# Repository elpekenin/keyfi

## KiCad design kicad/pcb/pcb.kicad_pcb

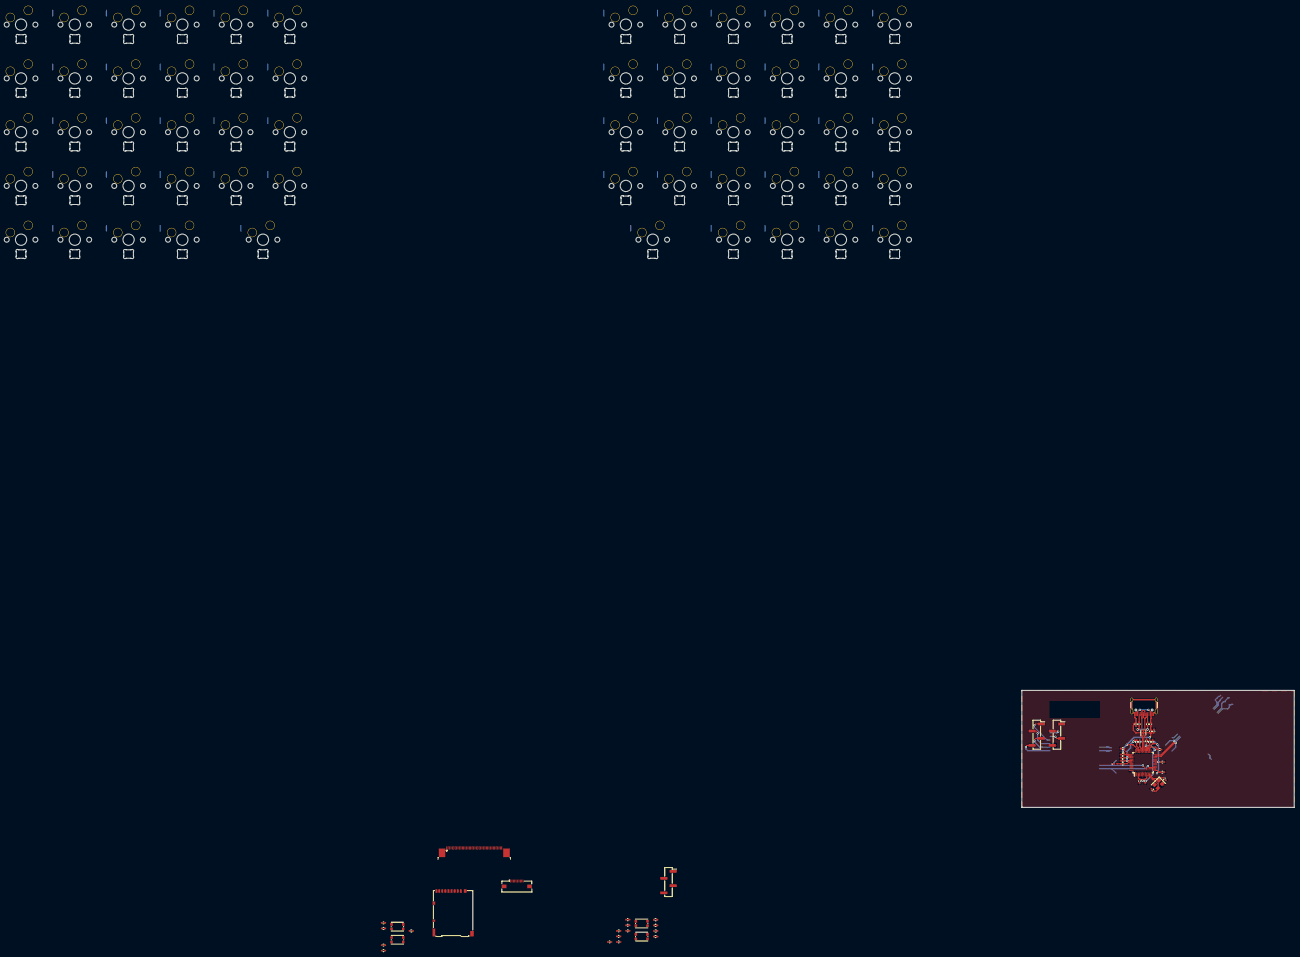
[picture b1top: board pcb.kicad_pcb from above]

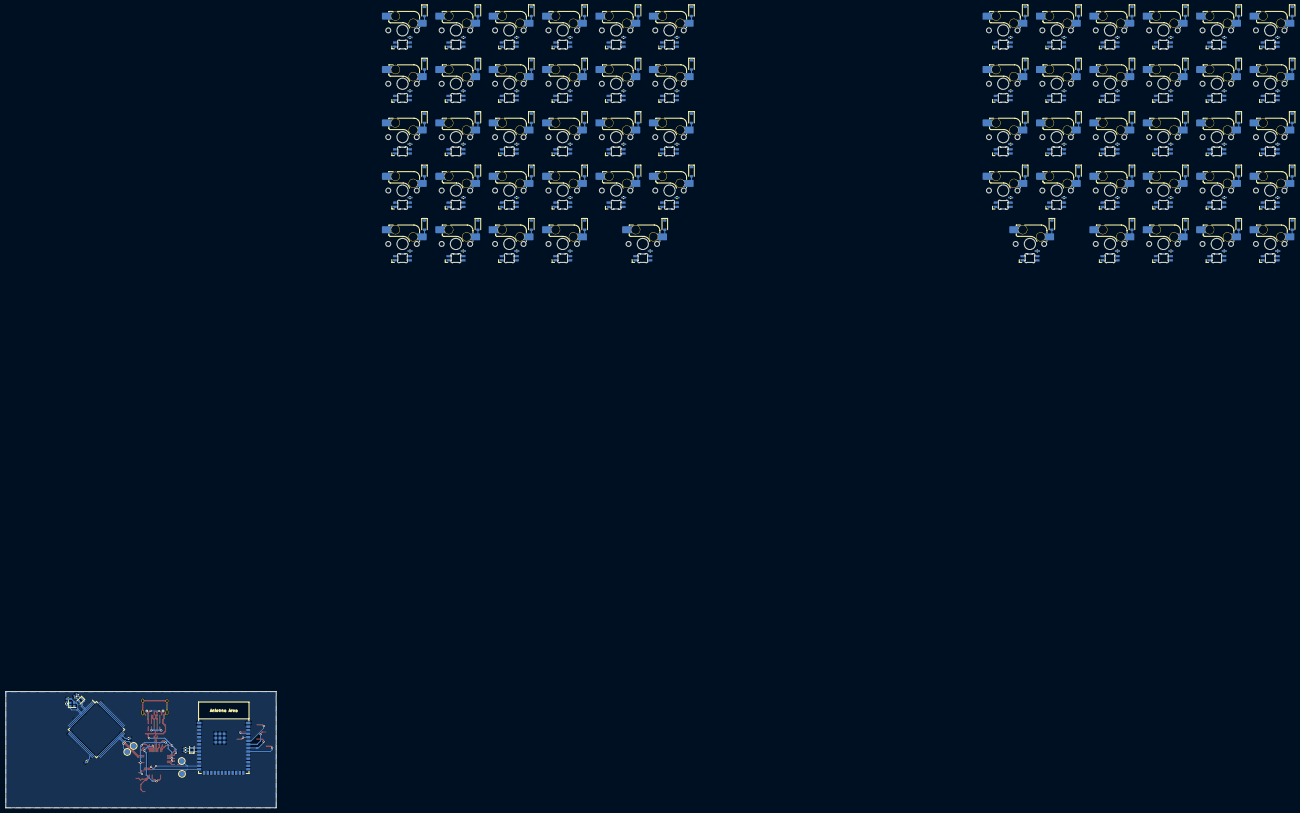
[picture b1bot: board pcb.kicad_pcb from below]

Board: 2 copper layers, 452.9 x 273.9 mm, 303 parts (249 on the bottom side), 212 nets.

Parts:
C1, C2, C3, C4, C5, C6, C7, C8, C9, C10, C11, C12, C13, C14, C15, C16, C17, C18, C19, C20, C21, C22, C23, C24, C25, C26, C27, C28, C29, C30, C31, C32, C33, C34, C35, C36, C37, C38, C39, C40, C41, C42, C43, C44, C45, C46, C47, C48, C49, C50, C51, C52, C53, C54, C55, C56, C57, C58, C64, C65, C68, C69, C70, C71, C73, C74, C75, C84, C87, C88, C89, C90, C91, C92: 100n; C_0402_1005Metric_Pad0.74x0.62mm_HandSolder
C59: 22u; C_0402_1005Metric_Pad0.74x0.62mm_HandSolder
C60, C79: 0.1u; C_0402_1005Metric_Pad0.74x0.62mm_HandSolder
C61, C63, C72: 10u; C_0402_1005Metric_Pad0.74x0.62mm_HandSolder
C66, C67, C76, C77: 12p; C_0402_1005Metric_Pad0.74x0.62mm_HandSolder
C78: C; C_0402_1005Metric_Pad0.74x0.62mm_HandSolder
C80, C81: 2.2u; C_0402_1005Metric_Pad0.74x0.62mm_HandSolder
C82, C83: 8p; C_0402_1005Metric_Pad0.74x0.62mm_HandSolder
C85, C86: 1.5p; C_0402_1005Metric_Pad0.74x0.62mm_HandSolder
D1, D2, D3, D4, D5, D6, D7, D8, D9, D10, D11, D12, D13, D14, D15, D16, D17, D18, D19, D20, D21, D22, D23, D24, D25, D26, D27, D28, D29, D30, D31, D32, D33, D34, D35, D36, D37, D38, D39, D40, D41, D42, D43, D44, D45, D46, D47, D48, D49, D50, D51, D52, D53, D54, D55, D56, D57, D58: 1N4148W; D_SOD-123
D59: HUB LED; LED_0402_1005Metric_Pad0.77x0.64mm_HandSolder
F1: 750 mA; Fuse_0402_1005Metric_Pad0.77x0.64mm_HandSolder
J1: ESP JTAG; PinHeader_1x04_P2.54mm_Vertical_SMD_Pin1Right
J2: USB Connector; USB_C_Receptacle_HRO_TYPE-C-31-M-12
J3: ESP UART; PinHeader_1x04_P2.54mm_Vertical_SMD_Pin1Right
J4: SD Card; microSD_HC_Hirose_DM3AT-SF-PEJM5
J5: LTDC Screen; TE_4-1734839-0_1x40-1MP_P0.5mm_Horizontal
J6: LS0XX; Molex_54548-1071_1x10-1MP_P0.5mm_Horizontal
J7: STM Debug; PinHeader_1x04_P2.54mm_Vertical_SMD_Pin1Right
L1, L2: L_Ferrite; L_0402_1005Metric_Pad0.77x0.64mm_HandSolder
LED1, LED2, LED3, LED4, LED5, LED6, LED7, LED8, LED9, LED10, LED11, LED12, LED13, LED14, LED15, LED16, LED17, LED18, LED19, LED20, LED21, LED22, LED23, LED24, LED25, LED26, LED27, LED28, LED29, LED30, LED31, LED32, LED33, LED34, LED35, LED36, LED37, LED38, LED39, LED40, LED41, LED42, LED43, LED44, LED45, LED46, LED47, LED48, LED49, LED50, LED51, LED52, LED53, LED54, LED55, LED56, LED57, LED58: MX_SK6812MINI-E; LED_MX_6028R
MX1, MX2, MX3, MX4, MX5, MX6, MX7, MX8, MX9, MX10, MX11, MX12, MX13, MX14, MX15, MX16, MX17, MX18, MX19, MX20, MX21, MX22, MX23, MX24, MX25, MX26, MX27, MX28, MX29, MX30, MX31, MX32, MX33, MX34, MX35, MX36, MX37, MX38, MX39, MX40, MX41, MX42, MX43, MX44, MX45, MX46, MX47, MX48, MX49, MX50, MX51, MX52, MX53, MX54, MX55, MX56, MX57, MX58: MX_SW_HS; SW_MX_HS_1u
R1, R9: R; R_0402_1005Metric_Pad0.72x0.64mm_HandSolder
R6: 2K7; R_0402_1005Metric_Pad0.72x0.64mm_HandSolder
R7, R13, R15, R18: 10K; R_0402_1005Metric_Pad0.72x0.64mm_HandSolder
R11, R12: 5K1; R_0402_1005Metric_Pad0.72x0.64mm_HandSolder
R16, R17: 22R; R_0402_1005Metric_Pad0.72x0.64mm_HandSolder
SW1: ESP Boot; SW_Push_1P1T_NO_CK_KMR2
SW2: ESP Rst; SW_Push_1P1T_NO_CK_KMR2
SW3: STM Boot; SW_Push_1P1T_NO_CK_KMR2
SW4: STM Rst; SW_Push_1P1T_NO_CK_KMR2
TP1, TP2, TP3, TP4: TestPoint; TestPoint_Pad_D2.0mm
U1: FE1.1; LQFP-48_7x7mm_P0.5mm
U2: STM32H750VBTx; LQFP-100_14x14mm_P0.5mm
U3: ESP32-S3-WROOM-2
U6: USBLC6-2P6; SOT-666
Y1: 12 MHz; Crystal_SMD_3225-4Pin_3.2x2.5mm
Y2, Y4: 32.768 KHz; Crystal_SMD_2012-2Pin_2.0x1.2mm
Y3: 25 MHz; Crystal_SMD_2016-4Pin_2.0x1.6mm

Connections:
+3V3: C59.1, C60.1, C84.1, C87.1, C88.1, C89.1, C90.1, C91.1, C92.1, J3.1, J4.4 (VDD), J5.4, J7.1, R9.1, R18.2, SW3.1, U2.6 (VBAT), U2.11 (VDD), U2.21 (VDDA), U2.27 (VDD), U2.50 (VDD), U2.75 (VDD), U2.100 (VDD), U3.2 (3V3)
+5V: C1.1, C2.1, C3.1, C4.1, C5.1, C6.1, C7.1, C8.1, C9.1, C10.1, C11.1, C12.1, C13.2, C14.2, C15.2, C16.2, C17.2, C18.2, C19.2, C20.2, C21.2, C22.2, C23.2, C24.2, C25.1, C26.1, C27.1, C28.1, C29.1, C30.1, C31.1, C32.1, C33.1, C34.1, C35.1, C36.1, C37.2, C38.2, C39.2, C40.2, C41.2, C42.2, C43.2, C44.2, C45.2, C46.2, C47.2, C48.2, C49.1, C50.1, C51.1, C52.1, C53.1, C54.1, C55.1, C56.1, C57.1, C58.1, C61.2, C65.2, F1.2, J5.1, J5.2, LED1.1 (VDD), LED2.1 (VDD), LED3.1 (VDD), LED4.1 (VDD), LED5.1 (VDD), LED6.1 (VDD), LED7.1 (VDD), LED8.1 (VDD), LED9.1 (VDD), LED10.1 (VDD), LED11.1 (VDD), LED12.1 (VDD), LED13.1 (VDD), LED14.1 (VDD), LED15.1 (VDD), LED16.1 (VDD), LED17.1 (VDD), LED18.1 (VDD), LED19.1 (VDD), LED20.1 (VDD), LED21.1 (VDD), LED22.1 (VDD), LED23.1 (VDD), LED24.1 (VDD), LED25.1 (VDD), LED26.1 (VDD), LED27.1 (VDD), LED28.1 (VDD), LED29.1 (VDD), LED30.1 (VDD), LED31.1 (VDD), LED32.1 (VDD), LED33.1 (VDD), LED34.1 (VDD), LED35.1 (VDD), LED36.1 (VDD), LED37.1 (VDD), LED38.1 (VDD), LED39.1 (VDD), LED40.1 (VDD), LED41.1 (VDD), LED42.1 (VDD), LED43.1 (VDD), LED44.1 (VDD), LED45.1 (VDD), LED46.1 (VDD), LED47.1 (VDD), LED48.1 (VDD), LED49.1 (VDD), LED50.1 (VDD), LED51.1 (VDD), LED52.1 (VDD), LED53.1 (VDD), LED54.1 (VDD), LED55.1 (VDD), LED56.1 (VDD), LED57.1 (VDD), LED58.1 (VDD), U1.35 (VBUSM), U1.38 (VD5_IN), U6.5 (VBUS)
COL_0: MX1.2, MX13.2, MX25.2, MX37.2, MX49.2
COL_1: MX2.2, MX14.2, MX26.2, MX38.2, MX50.2
COL_2: MX3.2, MX15.2, MX27.2, MX39.2, MX51.2
COL_3: MX4.2, MX16.2, MX28.2, MX40.2, MX52.2
COL_4: MX5.2, MX17.2, MX29.2, MX41.2, MX53.2
COL_5: MX6.2, MX18.2, MX30.2, MX42.2
COL_6: MX7.2, MX19.2, MX31.2, MX43.2, MX54.2
COL_7: MX8.2, MX20.2, MX32.2, MX44.2
COL_8: MX9.2, MX21.2, MX33.2, MX45.2, MX55.2
COL_9: MX10.2, MX22.2, MX34.2, MX46.2, MX56.2
COL_10: MX11.2, MX23.2, MX35.2, MX47.2, MX57.2
COL_11: MX12.2, MX24.2, MX36.2, MX48.2, MX58.2
ESP D+: TP3.1, U1.15 (DP4), U3.14 (GPIO20/U1CTS/ADC2_CH9/CLK_OUT1/USB_D+)
ESP D-: TP4.1, U1.14 (DM4), U3.13 (GPIO19/U1RTS/ADC2_CH8/CLK_OUT2/USB_D-)
ESP EN: C78.2, C79.2, R9.2, SW2.2, U3.3 (EN)
Earth: J2.A1 (GND), J2.A12 (GND), J2.B1 (GND), J2.B12 (GND), J2.S1 (SHIELD), L1.1, U6.2 (GND)
GND: C1.2, C2.2, C3.2, C4.2, C5.2, C6.2, C7.2, C8.2, C9.2, C10.2, C11.2, C12.2, C13.1, C14.1, C15.1, C16.1, C17.1, C18.1, C19.1, C20.1, C21.1, C22.1, C23.1, C24.1, C25.2, C26.2, C27.2, C28.2, C29.2, C30.2, C31.2, C32.2, C33.2, C34.2, C35.2, C36.2, C37.1, C38.1, C39.1, C40.1, C41.1, C42.1, C43.1, C44.1, C45.1, C46.1, C47.1, C48.1, C49.2, C50.2, C51.2, C52.2, C53.2, C54.2, C55.2, C56.2, C57.2, C58.2, C59.2, C60.2, C61.1, C63.2, C64.2, C65.1, C66.1, C67.2, C68.2, C69.2, C70.2, C71.2, C72.2, C73.2, C74.2, C75.2, C76.1, C77.2, C78.1, C79.1, C80.2, C81.1, C82.1, C83.2, C84.2, C85.1, C86.2, C87.2, C88.2, C89.2, C90.2, C91.2, C92.2, D59.1 (K), J3.4, J4.6 (VSS), J4.10 (SHIELD), J5.3, J5.29, J5.36, J7.4, L1.2, LED1.4 (VSS), LED2.4 (VSS), LED3.4 (VSS), LED4.4 (VSS), LED5.4 (VSS), LED6.4 (VSS), LED7.4 (VSS), LED8.4 (VSS), LED9.4 (VSS), LED10.4 (VSS), LED11.4 (VSS), LED12.4 (VSS), LED13.4 (VSS), LED14.4 (VSS), LED15.4 (VSS), LED16.4 (VSS), LED17.4 (VSS), LED18.4 (VSS), LED19.4 (VSS), LED20.4 (VSS), LED21.4 (VSS), LED22.4 (VSS), LED23.4 (VSS), LED24.4 (VSS), LED25.4 (VSS), LED26.4 (VSS), LED27.4 (VSS), LED28.4 (VSS), LED29.4 (VSS), LED30.4 (VSS), LED31.4 (VSS), LED32.4 (VSS), LED33.4 (VSS), LED34.4 (VSS), LED35.4 (VSS), LED36.4 (VSS), LED37.4 (VSS), LED38.4 (VSS), LED39.4 (VSS), LED40.4 (VSS), LED41.4 (VSS), LED42.4 (VSS), LED43.4 (VSS), LED44.4 (VSS), LED45.4 (VSS), LED46.4 (VSS), LED47.4 (VSS), LED48.4 (VSS), LED49.4 (VSS), LED50.4 (VSS), LED51.4 (VSS), LED52.4 (VSS), LED53.4 (VSS), LED54.4 (VSS), LED55.4 (VSS), LED56.4 (VSS), LED57.4 (VSS), LED58.4 (VSS), R6.1, R11.2, R12.2, R13.1, R15.2, SW1.2, SW2.1, SW4.1, U1.1 (OVCB[2]), U1.5 (OVCB[3]), U1.6 (VSS), U1.7 (OVCB[4]), U1.8 (PWRB[4]), U1.10 (VS_PLL), U1.16 (VSS), U1.22 (VSS), U1.25 (VS_A), U1.33 (VSS), U1.36 (BUS_B), U1.40 (TEST), U1.43 (LED[1]), U1.44 (LED[2]), U1.48 (OVCB[1]), U2.10 (VSS), U2.19 (VSSA), U2.26 (VSS), U2.49 (VSS), U2.74 (VSS), U2.99 (VSS), U3.1 (GND), U3.40 (GND), U3.41 (GND), Y1.2, Y1.4, Y3.2, Y3.4
HUB 1V8: C72.1, C73.1, C74.1, C75.1, U1.3 (VD18), U1.9 (VD_PLL), U1.26 (VREG18), U1.29 (VD18)
HUB 3V3: C63.1, C64.1, C68.1, C69.1, C70.1, C71.1, R7.1, U1.13 (VD33), U1.19 (VD33), U1.27 (VD3_IN), U1.32 (VD33), U1.39 (VD33_OUT), U1.41 (VD33)
HUB D+: U1.31 (DPU), U6.1 (I/O1)
HUB D-: U1.30 (DMU), U6.3 (I/O2)
LCD_B0: J5.21, U2.3 (PE4)
LCD_B1: J5.22, U2.69 (PA10)
LCD_B2: J5.23, U2.66 (PC9)
LCD_B3: J5.24, U2.57 (PD10)
LCD_B4: J5.25, U2.42 (PE12)
LCD_B5: J5.26, U2.25 (PA3)
LCD_B6: J5.27, U2.95 (PB8)
LCD_B7: J5.28, U2.96 (PB9)
LCD_CLK: J5.30, U2.44 (PE14)
LCD_DE: J5.34, U2.43 (PE13)
LCD_G0: J5.13, U2.4 (PE5)
LCD_G1: J5.14, U2.5 (PE6)
LCD_G2: J5.15, U2.30 (PA6)
LCD_G3: J5.16, U2.41 (PE11)
LCD_G4: J5.17, U2.46 (PB10)
LCD_G5: J5.18, U2.47 (PB11)
LCD_G6: J5.19, U2.64 (PC7)
LCD_G7: J5.20, U2.84 (PD3)
LCD_HSYNC: J5.32, U2.63 (PC6)
LCD_R1: J5.6, U2.24 (PA2)
LCD_R2: J5.7, U2.23 (PA1)
LCD_R3: J5.8, U2.34 (PB0)
LCD_R4: J5.9, U2.29 (PA5)
LCD_R5: J5.10, U2.15 (PC0)
LCD_R6: J5.11, U2.35 (PB1)
LCD_R7: J5.12, U2.45 (PE15)
LCD_VSYNC: J5.33, U2.28 (PA4)
unnamed: C80.1, U2.73 (VCAP)
unnamed: C81.2, U2.48 (VCAP)
unnamed: D1.2 (A), MX1.1
unnamed: D2.2 (A), MX2.1
unnamed: D3.2 (A), MX3.1
unnamed: D4.2 (A), MX4.1
unnamed: D5.2 (A), MX5.1
unnamed: D6.2 (A), MX6.1
unnamed: D7.2 (A), MX7.1
unnamed: D8.2 (A), MX8.1
unnamed: D9.2 (A), MX9.1
unnamed: D10.2 (A), MX10.1
unnamed: D11.2 (A), MX11.1
unnamed: D12.2 (A), MX12.1
unnamed: D13.2 (A), MX13.1
unnamed: D14.2 (A), MX14.1
unnamed: D15.2 (A), MX15.1
unnamed: D16.2 (A), MX16.1
unnamed: D17.2 (A), MX17.1
unnamed: D18.2 (A), MX18.1
unnamed: D19.2 (A), MX19.1
unnamed: D20.2 (A), MX20.1
unnamed: D21.2 (A), MX21.1
unnamed: D22.2 (A), MX22.1
unnamed: D23.2 (A), MX23.1
unnamed: D24.2 (A), MX24.1
unnamed: D25.2 (A), MX25.1
unnamed: D26.2 (A), MX26.1
unnamed: D27.2 (A), MX27.1
unnamed: D28.2 (A), MX28.1
unnamed: D29.2 (A), MX29.1
unnamed: D30.2 (A), MX30.1
unnamed: D31.2 (A), MX31.1
unnamed: D32.2 (A), MX32.1
unnamed: D33.2 (A), MX33.1
unnamed: D34.2 (A), MX34.1
unnamed: D35.2 (A), MX35.1
unnamed: D36.2 (A), MX36.1
unnamed: D37.2 (A), MX37.1
unnamed: D38.2 (A), MX38.1
unnamed: D39.2 (A), MX39.1
unnamed: D40.2 (A), MX40.1
unnamed: D41.2 (A), MX41.1
unnamed: D42.2 (A), MX42.1
unnamed: D43.2 (A), MX43.1
unnamed: D44.2 (A), MX44.1
unnamed: D45.2 (A), MX45.1
unnamed: D46.2 (A), MX46.1
unnamed: D47.2 (A), MX47.1
unnamed: D48.2 (A), MX48.1
unnamed: D49.2 (A), MX49.1
unnamed: D50.2 (A), MX50.1
unnamed: D51.2 (A), MX51.1
unnamed: D52.2 (A), MX52.1
unnamed: D53.2 (A), MX53.1
unnamed: D54.2 (A), MX54.1
unnamed: D55.2 (A), MX55.1
unnamed: D56.2 (A), MX56.1
unnamed: D57.2 (A), MX57.1
unnamed: D58.2 (A), MX58.1
unnamed: D59.2 (A), R1.2
unnamed: F1.1, L2.2
unnamed: J1.1, U3.35 (MTMS/GPIO42)
unnamed: J1.2, U3.34 (MTDI/GPIO41/CLK_OUT1)
unnamed: J1.3, U3.33 (MTDO/GPIO40/CLK_OUT2)
unnamed: J1.4, U3.32 (MTCK/GPIO39/CLK_OUT3/SUBSPICS1)
unnamed: J2.A5 (CC1), R11.1
unnamed: J2.B5 (CC2), R12.1
unnamed: J2.A4 (VBUS), J2.A9 (VBUS), J2.B4 (VBUS), J2.B9 (VBUS), L2.1
unnamed: J3.2, U3.37 (U0TXD/GPIO43/CLK_OUT1)
unnamed: J3.3, U3.36 (U0RXD/GPIO44/CLK_OUT2)
unnamed: LED1.2 (DOUT), LED2.3 (DIN)
unnamed: LED2.2 (DOUT), LED3.3 (DIN)
unnamed: LED3.2 (DOUT), LED4.3 (DIN)
unnamed: LED4.2 (DOUT), LED5.3 (DIN)
unnamed: LED5.2 (DOUT), LED6.3 (DIN)
unnamed: LED6.2 (DOUT), LED7.3 (DIN)
unnamed: LED7.2 (DOUT), LED8.3 (DIN)
unnamed: LED8.2 (DOUT), LED9.3 (DIN)
unnamed: LED9.2 (DOUT), LED10.3 (DIN)
unnamed: LED10.2 (DOUT), LED11.3 (DIN)
unnamed: LED11.2 (DOUT), LED12.3 (DIN)
unnamed: LED12.2 (DOUT), LED13.3 (DIN)
unnamed: LED13.2 (DOUT), LED14.3 (DIN)
unnamed: LED14.2 (DOUT), LED15.3 (DIN)
unnamed: LED15.2 (DOUT), LED16.3 (DIN)
unnamed: LED16.2 (DOUT), LED17.3 (DIN)
unnamed: LED17.2 (DOUT), LED18.3 (DIN)
unnamed: LED18.2 (DOUT), LED19.3 (DIN)
unnamed: LED19.2 (DOUT), LED20.3 (DIN)
unnamed: LED20.2 (DOUT), LED21.3 (DIN)
unnamed: LED21.2 (DOUT), LED22.3 (DIN)
unnamed: LED22.2 (DOUT), LED23.3 (DIN)
unnamed: LED23.2 (DOUT), LED24.3 (DIN)
unnamed: LED24.2 (DOUT), LED25.3 (DIN)
unnamed: LED25.2 (DOUT), LED26.3 (DIN)
unnamed: LED26.2 (DOUT), LED27.3 (DIN)
unnamed: LED27.2 (DOUT), LED28.3 (DIN)
unnamed: LED28.2 (DOUT), LED29.3 (DIN)
unnamed: LED29.2 (DOUT), LED30.3 (DIN)
unnamed: LED30.2 (DOUT), LED31.3 (DIN)
unnamed: LED31.2 (DOUT), LED32.3 (DIN)
unnamed: LED32.2 (DOUT), LED33.3 (DIN)
unnamed: LED33.2 (DOUT), LED34.3 (DIN)
unnamed: LED34.2 (DOUT), LED35.3 (DIN)
unnamed: LED35.2 (DOUT), LED36.3 (DIN)
unnamed: LED36.2 (DOUT), LED37.3 (DIN)
unnamed: LED37.2 (DOUT), LED38.3 (DIN)
unnamed: LED38.2 (DOUT), LED39.3 (DIN)
unnamed: LED39.2 (DOUT), LED40.3 (DIN)
unnamed: LED40.2 (DOUT), LED41.3 (DIN)
unnamed: LED41.2 (DOUT), LED42.3 (DIN)
unnamed: LED42.2 (DOUT), LED43.3 (DIN)
unnamed: LED43.2 (DOUT), LED44.3 (DIN)
unnamed: LED44.2 (DOUT), LED45.3 (DIN)
unnamed: LED45.2 (DOUT), LED46.3 (DIN)
unnamed: LED46.2 (DOUT), LED47.3 (DIN)
unnamed: LED47.2 (DOUT), LED48.3 (DIN)
unnamed: LED48.2 (DOUT), LED49.3 (DIN)
unnamed: LED49.2 (DOUT), LED50.3 (DIN)
unnamed: LED50.2 (DOUT), LED51.3 (DIN)
unnamed: LED51.2 (DOUT), LED52.3 (DIN)
unnamed: LED52.2 (DOUT), LED53.3 (DIN)
unnamed: LED53.2 (DOUT), LED54.3 (DIN)
unnamed: LED54.2 (DOUT), LED55.3 (DIN)
unnamed: LED55.2 (DOUT), LED56.3 (DIN)
unnamed: LED56.2 (DOUT), LED57.3 (DIN)
unnamed: LED57.2 (DOUT), LED58.3 (DIN)
unnamed: R13.2, U1.37 (DIS_REG)
unnamed: R1.1, U1.42 (DRV)
unnamed: R6.2, U1.28 (REXT)
unnamed: C67.1, U1.12 (XIN), Y1.1
unnamed: C66.2, U1.11 (XOUT), Y1.3
unnamed: R7.2, U1.34 (XRSTJ)
unnamed: R17.1, U2.72 (PA13)
unnamed: R16.2, U2.76 (PA14)
unnamed: C86.1, U2.8 (PC14), Y4.1
unnamed: C85.2, U2.9 (PC15), Y4.2
unnamed: C82.2, U2.12 (PH0), Y3.3
unnamed: C83.1, U2.13 (PH1), Y3.1
unnamed: SW1.1, U3.27 (GPIO0/BOOT)
unnamed: C76.2, U3.8 (GPIO15/U0RTS/ADC2_CH4/XTAL_32K_P), Y2.2
unnamed: C77.1, U3.9 (GPIO16/U0CTS/ADC2_CH5/XTAL_32K_N), Y2.1
ROW_0: D1.1 (K), D2.1 (K), D3.1 (K), D4.1 (K), D5.1 (K), D6.1 (K), D7.1 (K), D8.1 (K), D9.1 (K), D10.1 (K), D11.1 (K), D12.1 (K)
ROW_1: D13.1 (K), D14.1 (K), D15.1 (K), D16.1 (K), D17.1 (K), D18.1 (K), D19.1 (K), D20.1 (K), D21.1 (K), D22.1 (K), D23.1 (K), D24.1 (K)
ROW_2: D25.1 (K), D26.1 (K), D27.1 (K), D28.1 (K), D29.1 (K), D30.1 (K), D31.1 (K), D32.1 (K), D33.1 (K), D34.1 (K), D35.1 (K), D36.1 (K)
ROW_3: D37.1 (K), D38.1 (K), D39.1 (K), D40.1 (K), D41.1 (K), D42.1 (K), D43.1 (K), D44.1 (K), D45.1 (K), D46.1 (K), D47.1 (K), D48.1 (K)
ROW_4: D49.1 (K), D50.1 (K), D51.1 (K), D52.1 (K), D53.1 (K), D54.1 (K), D55.1 (K), D56.1 (K), D57.1 (K), D58.1 (K)
SD CK: J4.5 (CLK), U2.87 (PD6)
SD CMD: J4.3 (CMD), U2.88 (PD7)
SD D0: J4.7 (DAT0), U2.53 (PB14)
SD D1: J4.8 (DAT1), U2.54 (PB15)
SD D2: J4.1 (DAT2), U2.89 (PB3)
SD D3: J4.2 (DAT3/CD), U2.90 (PB4)
STM Boot: R15.1, SW3.2, U2.94 (BOOT0)
STM D+: TP1.1, U1.24 (DP1), U2.71 (PA12)
STM D-: TP2.1, U1.23 (DM1), U2.70 (PA11)
STM Rst: R18.1, SW4.2, U2.14 (NRST)
SWCLK: J7.3, R16.1
SWDIO: J7.2, R17.2
USB D+: J2.A6 (D+), J2.B6 (D+), U6.6 (I/O1)
USB D-: J2.A7 (D-), J2.B7 (D-), U6.4 (I/O2)

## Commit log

2023-10-27 (WIP) Initial commit
2023-10-28 USB (almost) done + some STM progress
2023-10-29 Initial support circuitry for STM and ESP
2023-10-30 Initial wiring sorted out?
2023-11-01 Hub wired(?) + STM and ESP may boot already
2023-11-06 (WIP) Tracing v2
2023-11-12 Initial setup for firmware building
